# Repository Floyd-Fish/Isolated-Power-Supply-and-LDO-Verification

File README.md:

# Isolated-Power-Supply-and-LDO-Verification
隔离电源+高性能LDO评估板(KiCad工程)

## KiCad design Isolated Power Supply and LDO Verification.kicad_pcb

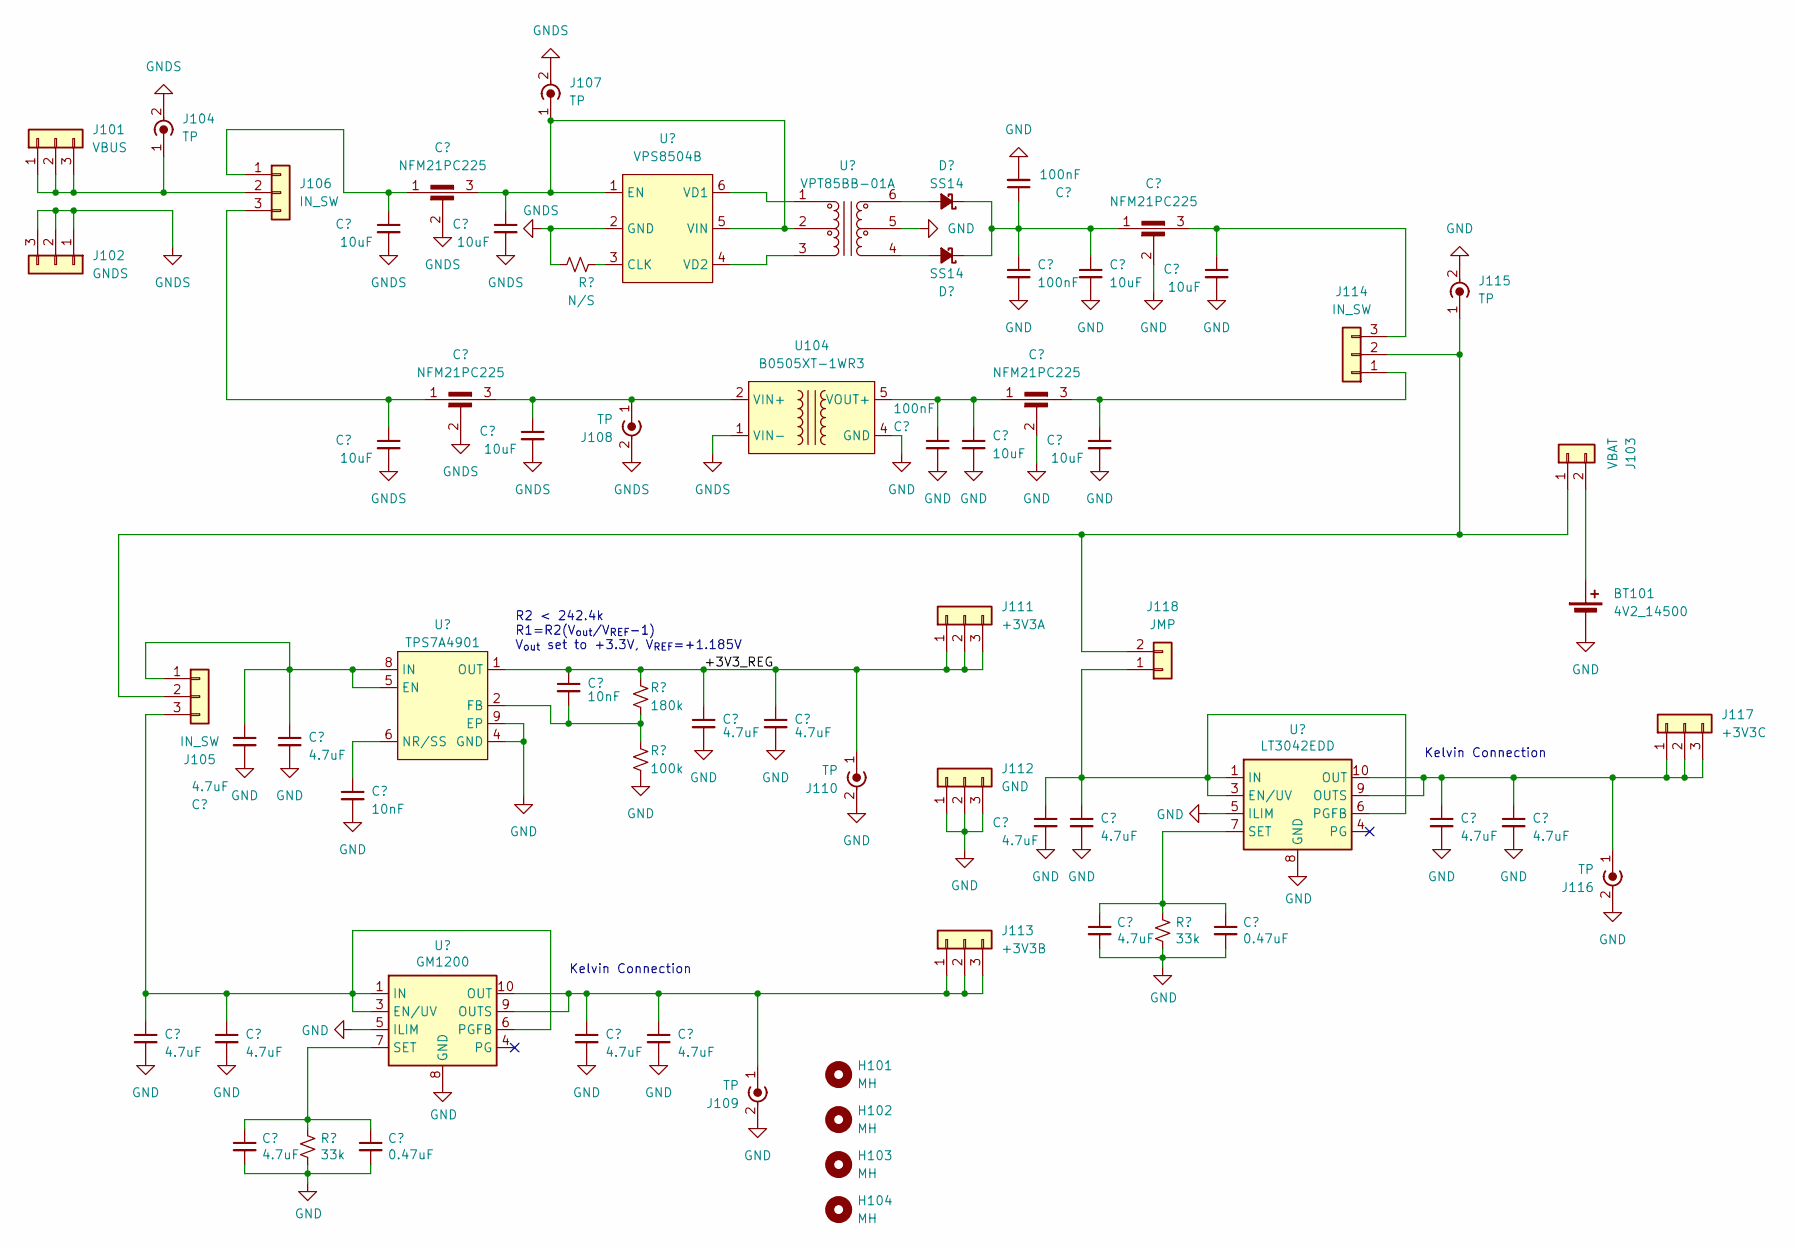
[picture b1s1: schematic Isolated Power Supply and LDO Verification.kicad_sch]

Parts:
BT101: 4V2_14500; PinHeader_1x02_P2.54mm_Vertical
C101, C102, C103, C113, C114, C115, C116, C125, C126, C128, C129, C130, C132, C133: 4.7uF; C_0805_2012Metric
C104, C112: 10nF; C_0402_1005Metric
C105, C127: 0.47uF; C_0402_1005Metric
C106, C107, C108, C109, C117, C121, C122, C124: 10uF; C_1206_3216Metric
C110, C111, C120, C123: NFM21PC225; NFM21PC225B0J3D
C118, C119, C131: 100nF; C_0603_1608Metric
D101, D102: SS14; D_SOD-123F
H101, H102, H103, H104: MH; MountingHole_3.2mm_M3_DIN965
J101: VBUS; PinHeader_1x03_P2.54mm_Vertical
J102: GNDS; PinHeader_1x03_P2.54mm_Vertical
J103: VBAT; PinHeader_1x02_P2.54mm_Vertical
J104, J107, J108, J109, J110, J115, J116: TP; SMA_Amphenol_132134_Vertical
J105, J106, J114: IN_SW; PinHeader_1x03_P2.54mm_Vertical
J111: +3V3A; PinHeader_1x03_P2.54mm_Vertical
J112: GND; PinHeader_1x03_P2.54mm_Vertical
J113: +3V3B; PinHeader_1x03_P2.54mm_Vertical
J117: +3V3C; PinHeader_1x03_P2.54mm_Vertical
J118: JMP; PinHeader_1x02_P2.54mm_Vertical
R101, R105: 33k; R_0402_1005Metric
R102: N/S; R_0402_1005Metric
R103: 180k; R_0402_1005Metric
R104: 100k; R_0402_1005Metric
U101: TPS7A4901; MSOP-8-1EP_3x3mm_P0.65mm_EP1.95x2.15mm
U102: GM1200; MSOP-10-1EP_3x3mm_P0.5mm_EP1.68x1.88mm
U103: VPS8504B; SOT-23-6
U104: B0505XT-1WR3; B0505XT-1W
U105: VPT85BB-01A; VPT85XX-0XA
U106: LT3042EDD; DFN-10-1EP_3x3mm_P0.5mm_EP1.65x2.38mm

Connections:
/+3V3_REG: C112.1, C115.1, C116.1, J110.1 (In), J111.1, J111.2, J111.3, R103.1, U101.1 (OUT)
GND: BT101.2 (-), C101.2, C102.2, C103.2, C104.2, C105.2, C113.2, C114.2, C115.2, C116.2, C117.2, C118.2, C119.2, C120.2, C121.2, C122.2, C123.2, C124.2, C125.2, C126.2, C127.2, C128.2, C129.2, C130.2, C131.2, C132.2, C133.2, J109.2 (Ext), J110.2 (Ext), J112.1, J112.2, J112.3, J115.2 (Ext), J116.2 (Ext), R101.1, R104.2, R105.1, U101.4 (GND), U101.9 (EP), U102.5 (ILIM), U102.8 (GND), U102.11 (GND), U104.4 (GND), U105.5, U106.5 (ILIM), U106.8 (GND), U106.11 (GND)
GNDS: C106.2, C107.2, C108.2, C109.2, C110.2, C111.2, J102.1, J102.2, J102.3, J104.2 (Ext), J107.2 (Ext), J108.2 (Ext), R102.1, U103.2 (GND), U104.1 (VIN-)
unnamed: BT101.1 (+), J103.2
unnamed: D101.2 (A), U105.6
unnamed: C118.1, C119.1, C121.1, C123.1, D101.1 (K), D102.1 (K)
unnamed: D102.2 (A), U105.4
unnamed: J101.1, J101.2, J101.3, J104.1 (In), J106.2
unnamed: J103.1, J105.2, J114.2, J115.1 (In), J118.2
unnamed: C103.1, C130.1, J105.1, U101.5 (EN), U101.8 (IN)
unnamed: C101.1, C133.1, J105.3, U102.1 (IN), U102.2 (IN), U102.3 (EN/UV), U102.6 (PGFB)
unnamed: C106.1, C110.1, J106.1
unnamed: C107.1, C111.1, J106.3
unnamed: C108.1, C110.3, J107.1 (In), U103.1 (EN), U103.5 (VIN), U105.2
unnamed: C109.1, C111.3, J108.1 (In), U104.2 (VIN+)
unnamed: C113.1, C114.1, J109.1 (In), J113.1, J113.2, J113.3, U102.9 (OUTS), U102.10 (OUT)
unnamed: C120.3, C122.1, J114.1
unnamed: C123.3, C124.1, J114.3
unnamed: C128.1, C129.1, J116.1 (In), J117.1, J117.2, J117.3, U106.9 (OUTS), U106.10 (OUT)
unnamed: C125.1, C132.1, J118.1, U106.1 (IN), U106.2 (IN), U106.3 (EN/UV), U106.6 (PGFB)
unnamed: C112.2, R103.2, R104.1, U101.2 (FB)
unnamed: C104.1, U101.6 (NR/SS)
unnamed: C102.1, C105.1, R101.2, U102.7 (SET)
unnamed: R102.2, U103.3 (CLK)
unnamed: U103.6 (VD1), U105.1
unnamed: U103.4 (VD2), U105.3
unnamed: C117.1, C120.1, C131.1, U104.5 (VOUT+)
unnamed: C126.1, C127.1, R105.2, U106.7 (SET)

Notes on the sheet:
Kelvin Connection
R2 < 242.4k R1=R2(V_{out}/V_{REF}-1) V_{out} set to +3.3V, V_{REF}=+1.185V

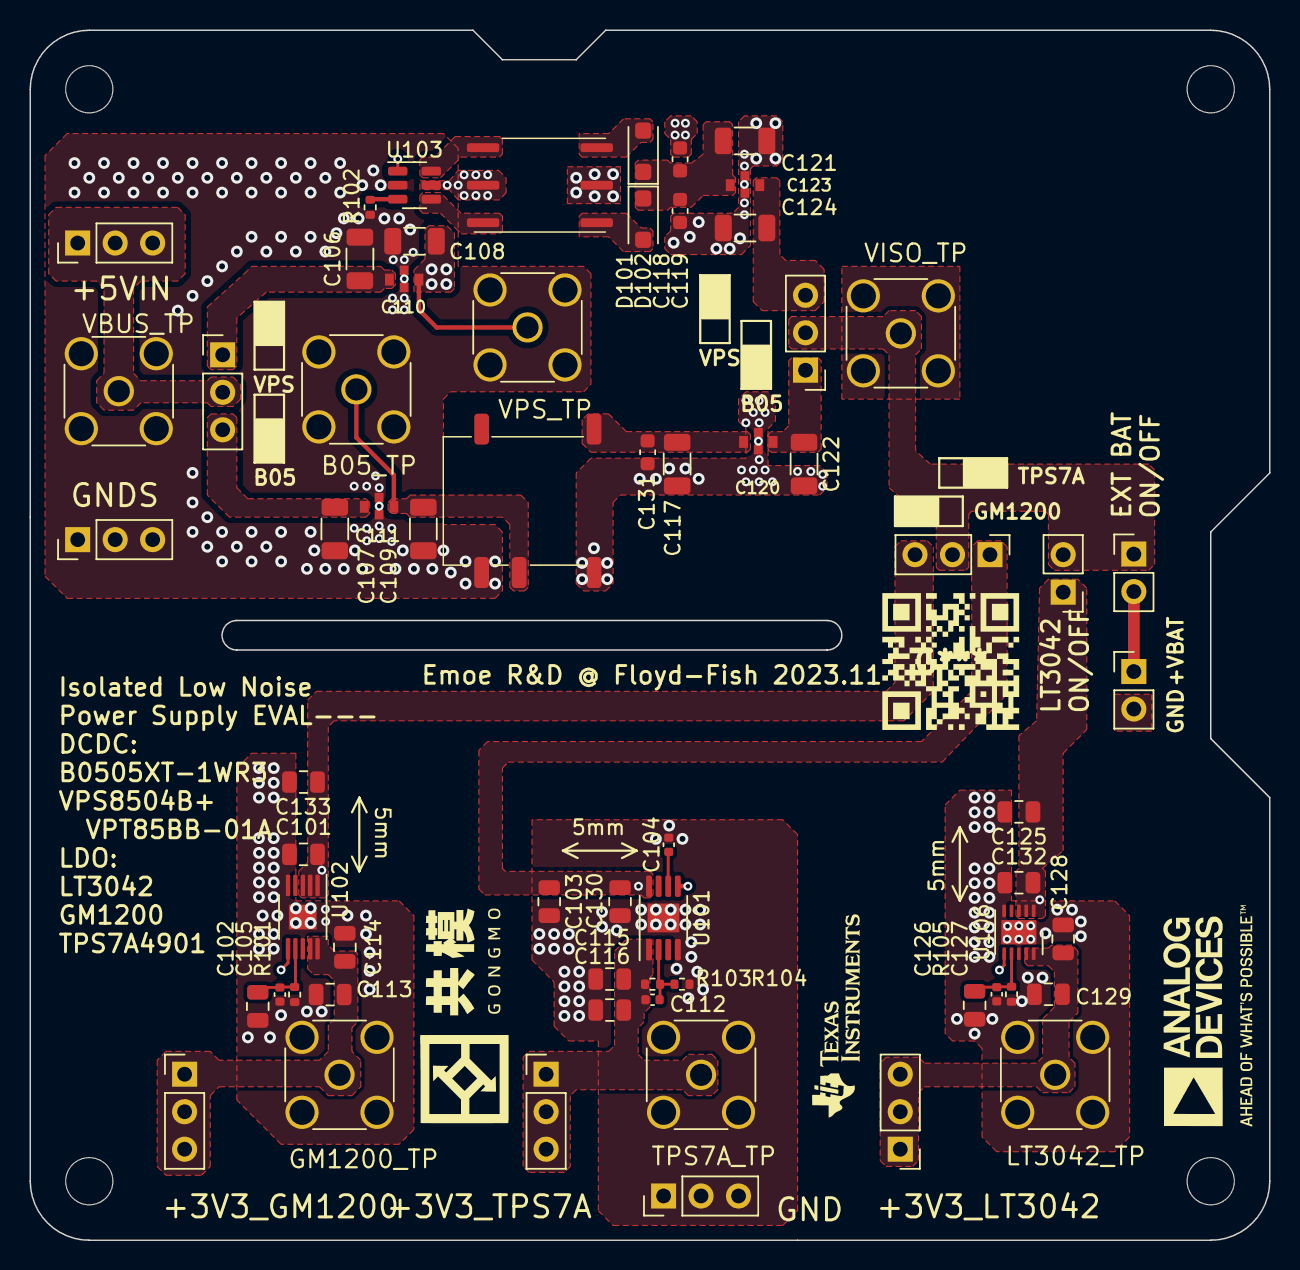
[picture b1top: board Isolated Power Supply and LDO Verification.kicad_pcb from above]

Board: 4 copper layers, 84.0 x 82.0 mm, 69 parts (0 on the bottom side), 28 nets.
